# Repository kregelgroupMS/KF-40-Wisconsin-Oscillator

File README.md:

This repository contains the materials needed to construct the KF 40 Wisconsin Oscillator circuit as described in this JASMS publication.
We intend this information to be freely available for academic researchers and students, but any entity intending to use these materials in a for-profit manner must contact the authors and receive permission for their use.

If you are interested in the original implementation of the Wisconsin Oscillator, please see follow this link for fabrication files and instructions: https://github.com/uw-madison-chem-shops/wisconsin-oscillator 

For questions, please contact us at sjkregel@fsmail.bradley.edu

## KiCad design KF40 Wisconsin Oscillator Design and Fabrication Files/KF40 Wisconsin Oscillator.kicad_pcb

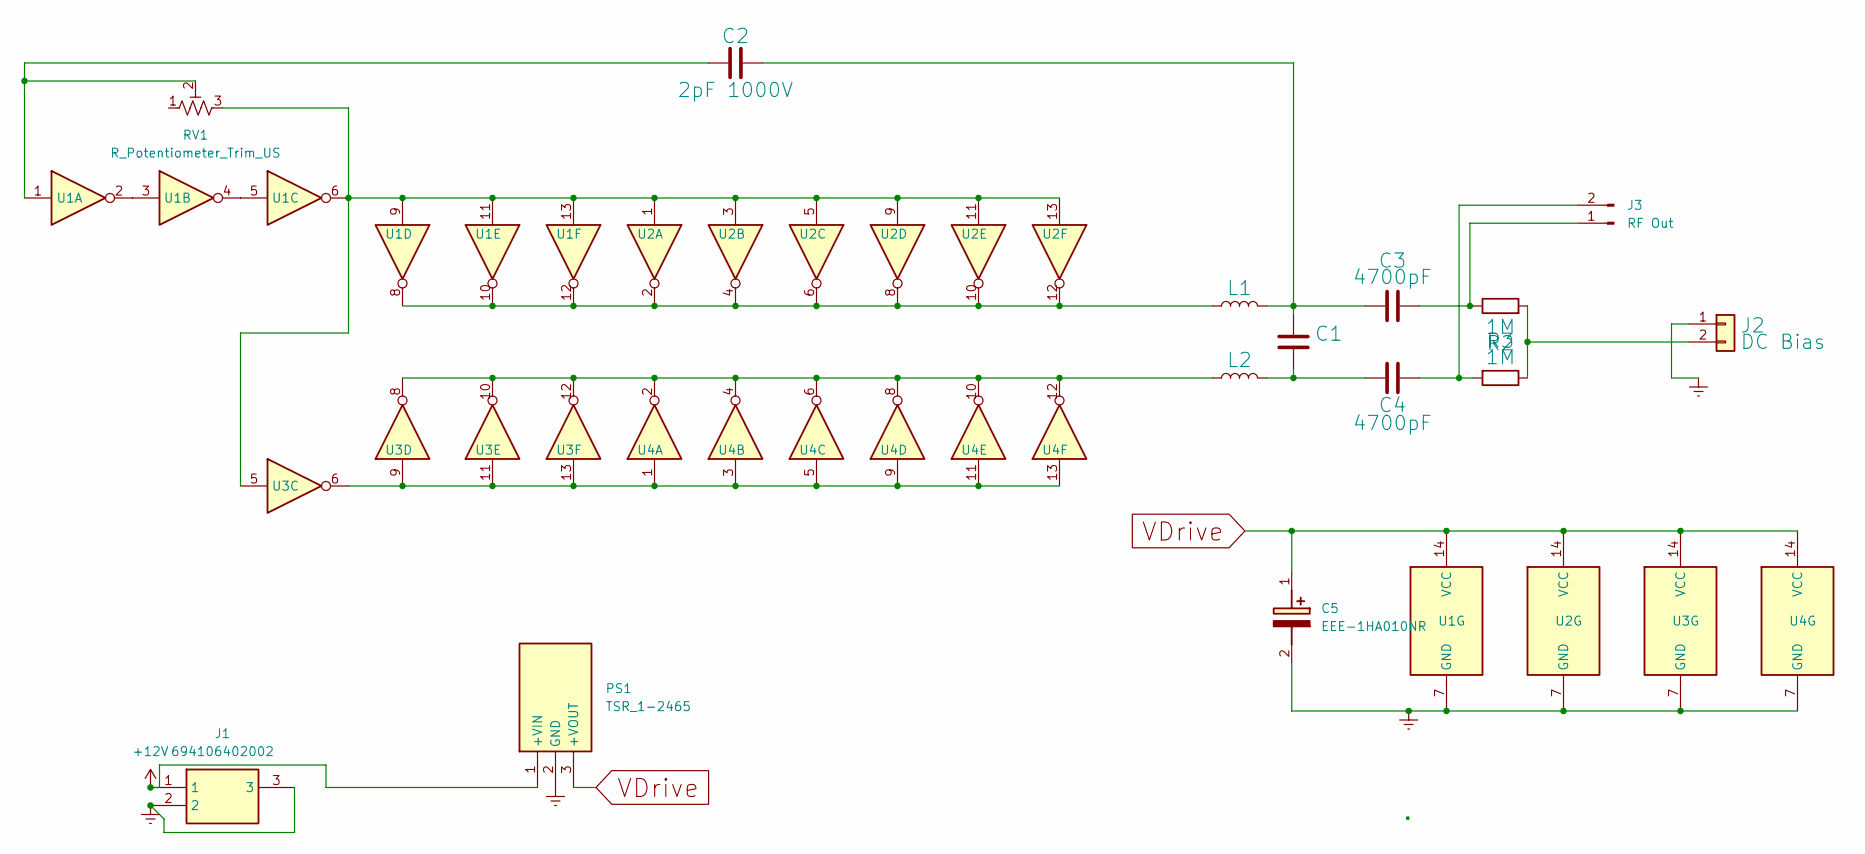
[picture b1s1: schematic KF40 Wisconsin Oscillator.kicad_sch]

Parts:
C1: 1000V; C_1206_3216Metric_Pad1.33x1.80mm_HandSolder
C2: 2pF 1000V; C_1206_3216Metric_Pad1.33x1.80mm_HandSolder
C3, C4: 4700pF; C_1206_3216Metric_Pad1.33x1.80mm_HandSolder
C5: EEE-1HA010NR; EEE1AA220WR; Manufacturer_Part_Number EEE-1HA010NR; Mouser Part Number 667-EEE-1HA010NR
J1: 694106402002; Manufacturer_Part_Number 694106402002; Mouser Part Number 710-694106402002
J2: DC Bias; PinHeader_1x02_P2.54mm_Vertical
J3: RF Out; PinHeader_1x02_P2.54mm_Vertical
L1, L2: 150uH (22R154C); L_Radial_D7.0mm_P3.00mm
PS1: TSR_1-2465; TSR-1-2433; Manufacturer_Part_Number TSR 1-2465; Mouser Part Number 495-TSR-1-2465
R2, R3: 1M; R_1206_3216Metric_Pad1.30x1.75mm_HandSolder
RV1: R_Potentiometer_Trim_US; Potentiometer_Bourns_3266W_Vertical
U1, U2, U3, U4: CD74AC04M96; SOIC-14_3.9x8.7mm_P1.27mm

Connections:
+12V: J1.1, PS1.1 (+VIN)
Earth: C5.2 (-), J1.2, J1.3, J2.1, PS1.2 (GND), U1.7 (GND), U2.7 (GND), U3.7 (GND), U4.7 (GND)
unnamed: C1.1, C2.2, C3.2, L1.2
unnamed: C1.2, C4.1, L2.2
unnamed: C2.1, RV1.2, U1.1
unnamed: J2.2, R2.2, R3.1
unnamed: C3.1, J3.1, R2.1
unnamed: C4.2, J3.2, R3.2
unnamed: L1.1, U1.8, U1.10, U1.12, U2.2, U2.4, U2.6, U2.8, U2.10, U2.12
unnamed: L2.1, U3.8, U3.10, U3.12, U4.2, U4.4, U4.6, U4.8, U4.10, U4.12
unnamed: RV1.3, U1.6, U1.9, U1.11, U1.13, U2.1, U2.3, U2.5, U2.9, U2.11, U2.13, U3.5
unnamed: U1.2, U1.3
unnamed: U1.4, U1.5
unnamed: U3.6, U3.9, U3.11, U3.13, U4.1, U4.3, U4.5, U4.9, U4.11, U4.13
VDrive: C5.1 (+), PS1.3 (+VOUT), U1.14 (VCC), U2.14 (VCC), U3.14 (VCC), U4.14 (VCC)

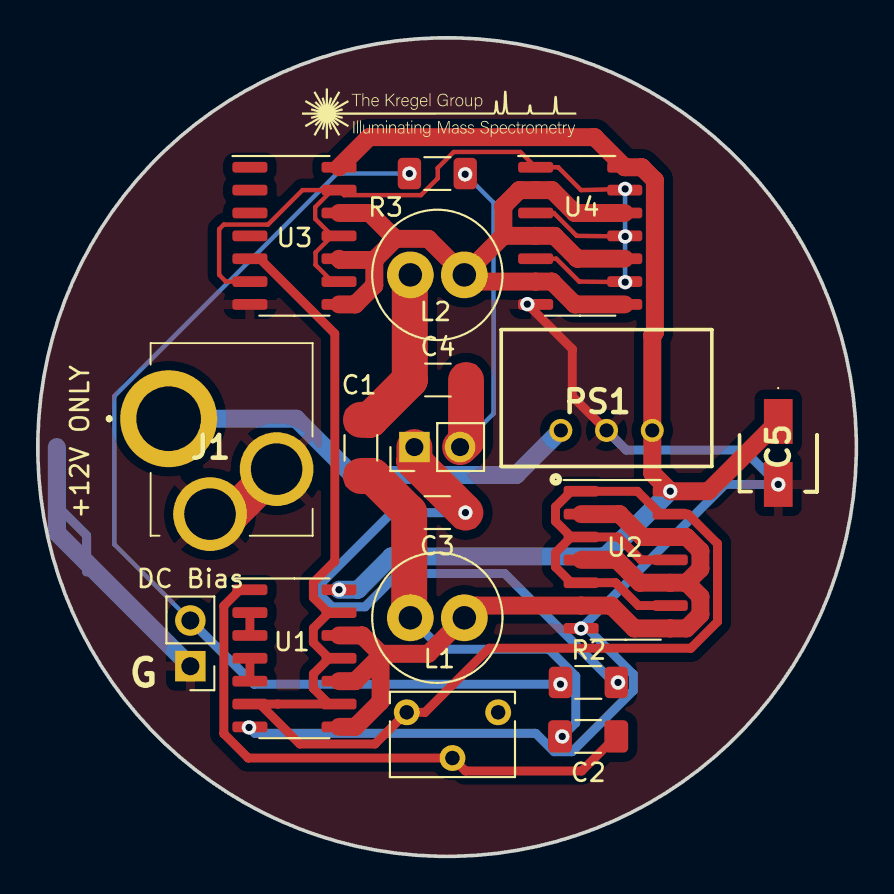
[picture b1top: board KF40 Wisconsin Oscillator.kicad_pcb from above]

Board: 2 copper layers, 45.5 x 45.5 mm, 18 parts (0 on the bottom side), 15 nets.
